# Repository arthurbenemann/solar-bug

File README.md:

# solar-bug
Based on https://github.com/rbaron/b-parasite

# License
The hardware and associated design files are released under the [Creative Commons CC BY-SA 4.0 license](https://creativecommons.org/licenses/by-sa/4.0/).
The code is released under the [MIT license](https://opensource.org/licenses/MIT).

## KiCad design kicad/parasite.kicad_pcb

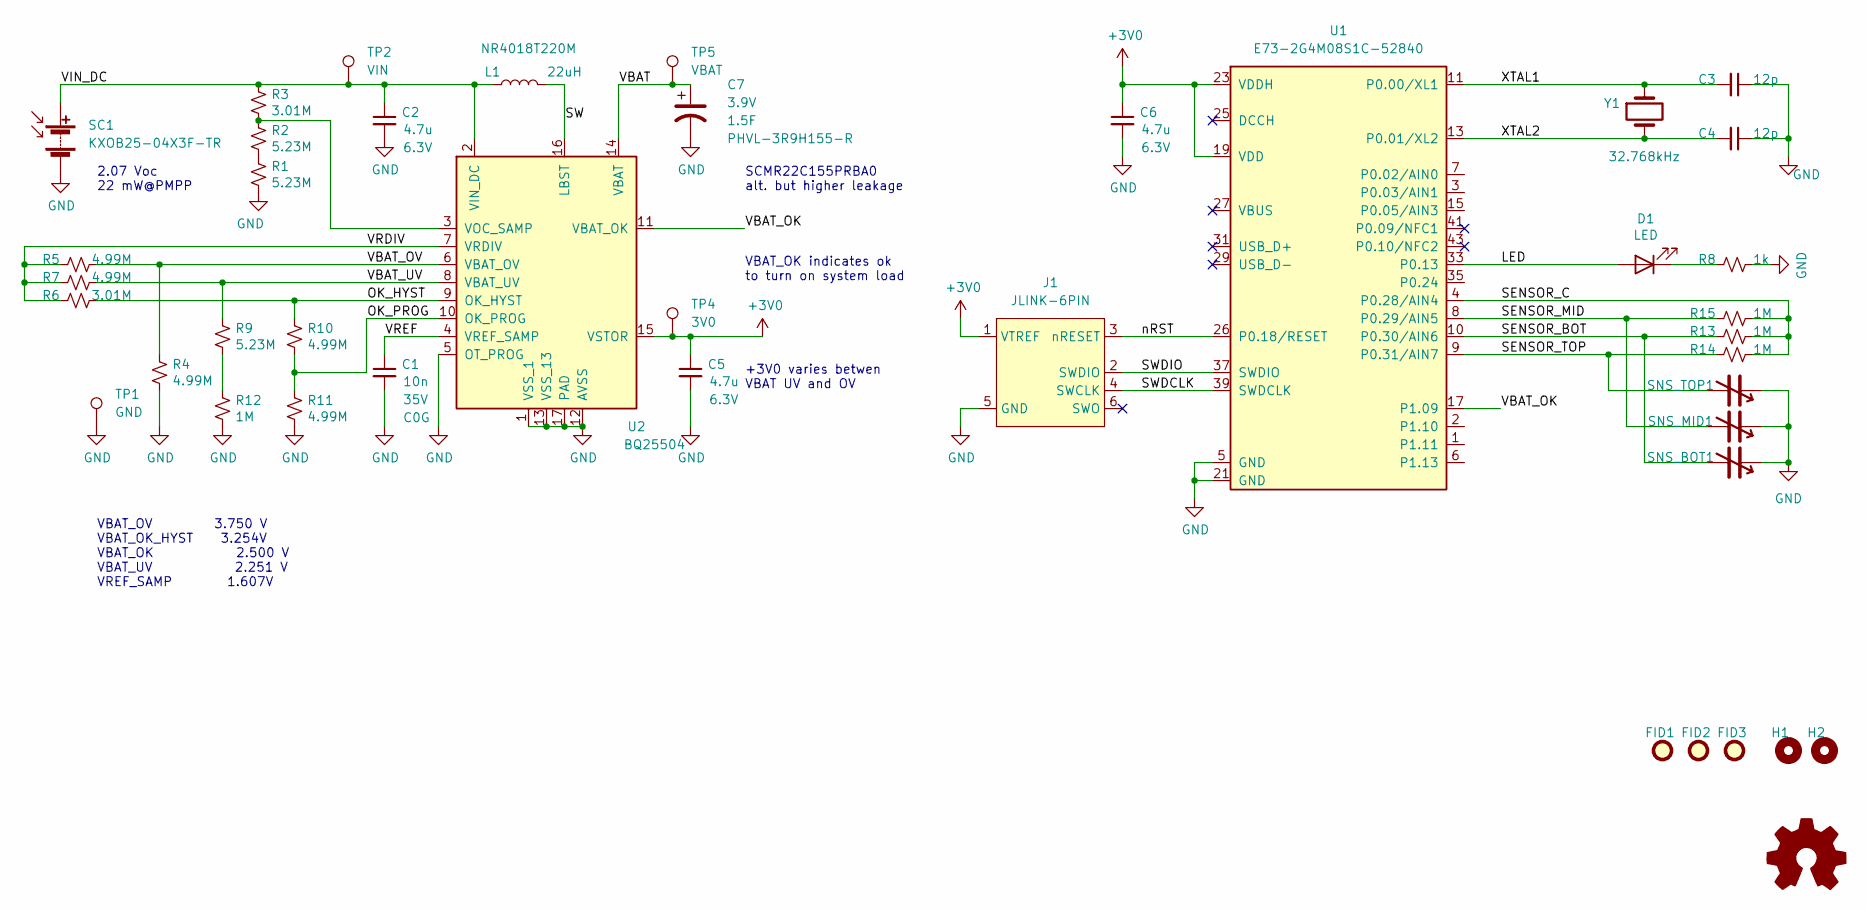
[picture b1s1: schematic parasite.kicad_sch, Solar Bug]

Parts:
C1: 10n; C_0402_1005Metric; Rating 35V; Tolerance C0G; LCSC C15195
C2, C5, C6: 4.7u; C_0402_1005Metric; Rating 6.3V; Tolerance x5R; LCSC C23733
C3, C4: 12p; C_0402_1005Metric; Tolerance x5R; LCSC C1547
C7: 1.5F; PHVL-3R9H155-R; Rating 3.9V; Tolerance x5R; MPN PHVL-3R9H155-R
D1: LED; LED_0402_1005Metric; Tolerance x5R; LCSC C160479
FID1, FID2, FID3: Fiducial; Fiducial_1mm_Mask2mm
H1, H2: MountingHole; MountingHole_1.1mm
J1: JLINK-6PIN; JLINK_6PIN
L1: 22uH; L_Taiyo-Yuden_NR-40xx; MPN NR4018T220M; LCSC C2880384
LOGO1: Logo_Open_Hardware_Small; OSHW-logo_silkscreen-front_10mm
R1, R2, R9: 5.23M; R_0402_1005Metric; Rating 1/16W; Tolerance 1%; LCSC C477747
R3, R6: 3.01M; R_0402_1005Metric; Rating 1/16W; Tolerance 1%; LCSC C163464
R4, R5, R7, R10, R11: 4.99M; R_0402_1005Metric; Rating 1/16W; Tolerance 1%; LCSC C137963
R8: 1k; R_0402_1005Metric; Rating 1/16W; Tolerance 1%; LCSC C11702
R12, R13, R14, R15: 1M; R_0402_1005Metric; Rating 1/16W; Tolerance 1%; LCSC C26083
SC1: KXOB25-04X3F-TR; KXOB25-04X3F; MPN KXOB25-04X3F-TR
SNS_BOT1: C_Variable; solar-bug-sensor
SNS_MID1: C_Variable; solar-bug-sensor
SNS_TOP1: C_Variable; solar-bug-sensor
TP1: GND; TestPoint_Pad_D0.75mm
TP2: VIN; TestPoint_Pad_D0.75mm
TP4: 3V0; TestPoint_Pad_D0.75mm
TP5: VBAT; TestPoint_Pad_D0.75mm
U1: E73-2G4M08S1C-52840; LCSC C356849
U2: BQ25504; VQFN-16-1EP_3x3mm_P0.5mm_EP1.8x1.8mm; LCSC C157471
Y1: 32.768kHz; Crystal_SMD_MicroCrystal_CM9V-T1A-2Pin_1.6x1.0mm; LCSC C398713

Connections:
+3V0: C5.1, C6.1, J1.1 (VTREF), TP4.1, U1.19 (VDD), U1.23 (VDDH), U2.15 (VSTOR)
/LED: D1.2 (A), U1.33 (P0.13)
/OK_HYST: R6.2, R10.1, U2.9 (OK_HYST)
/OK_PROG: R10.2, R11.1, U2.10 (OK_PROG)
/SENSOR_BOT: R13.1, SNS_BOT1.2, U1.10 (P0.30/AIN6)
/SENSOR_C: R13.2, R14.2, R15.2, U1.4 (P0.28/AIN4)
/SENSOR_MID: R15.1, SNS_MID1.2, U1.8 (P0.29/AIN5)
/SENSOR_TOP: R14.1, SNS_TOP1.2, U1.9 (P0.31/AIN7)
/SW: L1.2, U2.16 (LBST)
/SWDCLK: J1.4 (SWCLK), U1.39 (SWDCLK)
/SWDIO: J1.2 (SWDIO), U1.37 (SWDIO)
/VBAT: C7.1, TP5.1, U2.14 (VBAT)
/VBAT_OK: U1.17 (P1.09), U2.11 (VBAT_OK)
/VBAT_OV: R4.1, R5.2, U2.6 (VBAT_OV)
/VBAT_UV: R7.2, R9.1, U2.8 (VBAT_UV)
/VIN_DC: C2.1, L1.1, R3.1, SC1.1 (+), TP2.1, U2.2 (VIN_DC)
/VRDIV: R5.1, R6.1, R7.1, U2.7 (VRDIV)
/VREF: C1.1, U2.4 (VREF_SAMP)
/XTAL1: C3.2, U1.11 (P0.00/XL1), Y1.1
/XTAL2: C4.2, U1.13 (P0.01/XL2), Y1.2
/nRST: J1.3 (nRESET), U1.26 (P0.18/RESET)
GND: C1.2, C2.2, C3.1, C4.1, C5.2, C6.2, C7.2, J1.5 (GND), R1.2, R4.2, R8.2, R11.2, R12.2, SC1.2 (-), SNS_BOT1.1, SNS_MID1.1, SNS_TOP1.1, TP1.1, U1.5 (GND), U1.21 (GND), U2.1 (VSS_1), U2.5 (OT_PROG), U2.12 (AVSS), U2.13 (VSS_13), U2.17 (PAD)
unnamed: D1.1 (K), R8.1
unnamed: R1.1, R2.2
unnamed: R2.1, R3.2, U2.3 (VOC_SAMP)
unnamed: R9.2, R12.1

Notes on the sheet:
VBAT_OK indicates ok to turn on system load
2.07 Voc 22 mW@PMPP
VBAT_OV 3.750 V VBAT_OK_HYST 3.254V VBAT_OK 2.500 V VBAT_UV 2.251 V VREF_SAMP 1.607V
+3V0 varies betwen VBAT UV and OV
SCMR22C155PRBA0 alt. but higher leakage

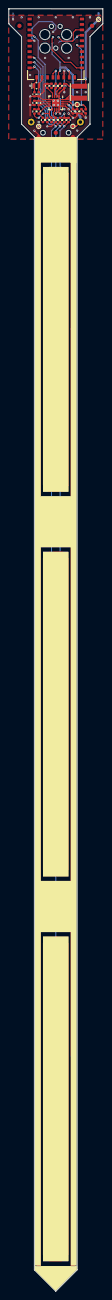
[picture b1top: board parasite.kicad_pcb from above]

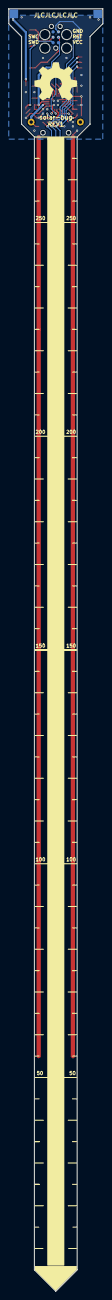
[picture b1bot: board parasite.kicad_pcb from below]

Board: 2 copper layers, 22.0 x 300.0 mm, 42 parts (4 on the bottom side), 26 nets.

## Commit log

2022-12-10 Cleared remaining DRC, add JLCPCB part numbers
2022-12-10 clean-up folder, renamed project file
2022-12-12 Add Digikey PNs to BOM, generate BOM CSV
2023-01-07 Add nrf52 internal temperature measurament
2023-01-07 add senosr reading on main loop
2023-01-07 change advertisement interval
2023-01-07 workspace changes to be able to compile
2023-01-11 remove sensors not present on solarbug, change encoding, correct led pin, change device name
2023-01-11 remove application added by mistake
2023-01-11 baseline ble blinky
2023-01-11 test adc
    # Conflicts:
    # code/nrf-connect/samples/ble/src/main.c
2023-02-04 add initial capacitive sense
